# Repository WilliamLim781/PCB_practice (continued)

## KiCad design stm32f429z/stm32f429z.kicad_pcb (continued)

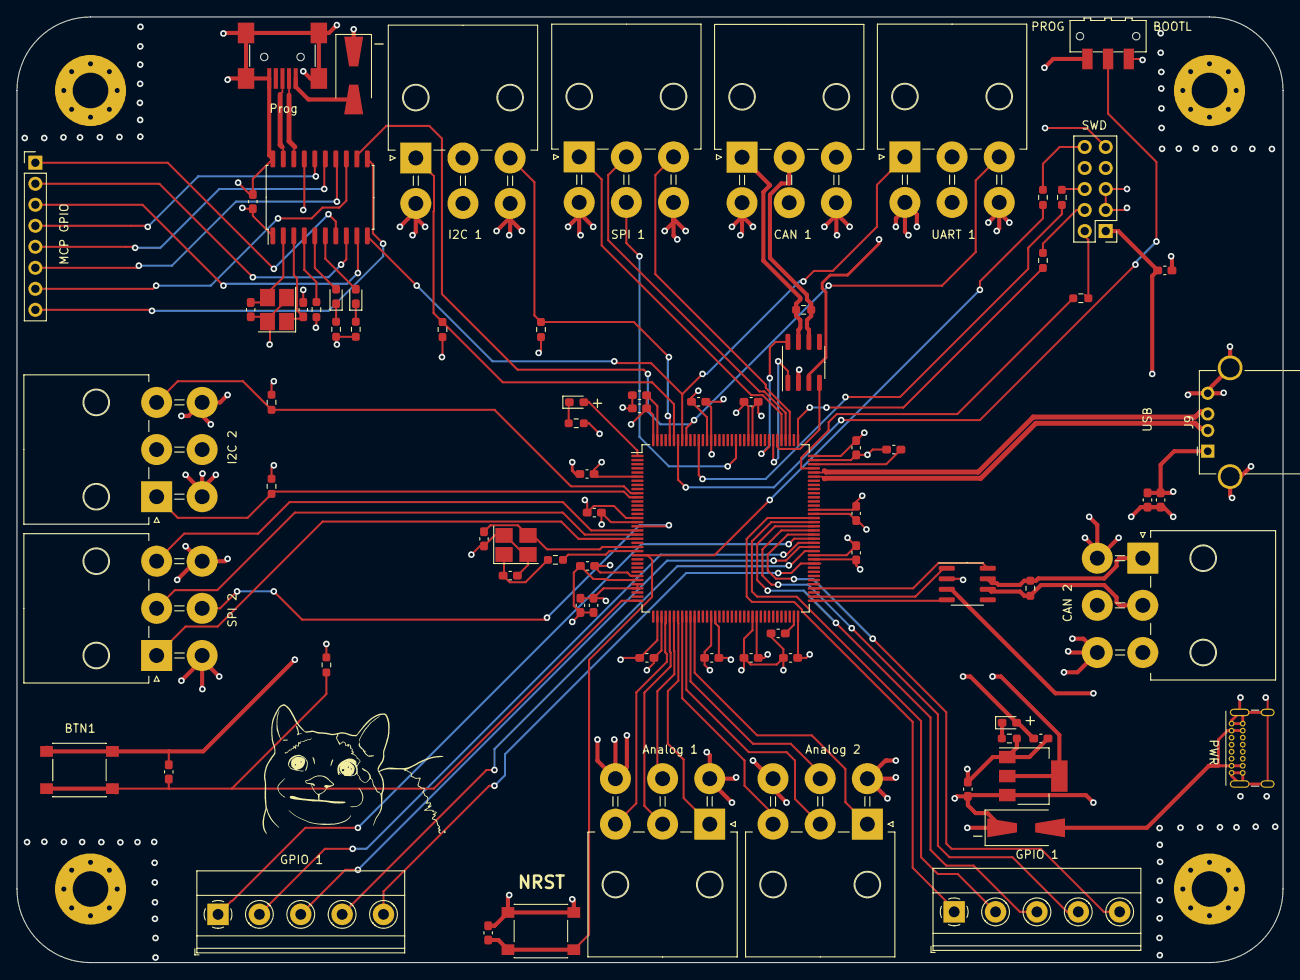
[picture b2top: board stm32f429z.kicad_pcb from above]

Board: 4 copper layers, 153.0 x 114.3 mm, 83 parts (0 on the bottom side), 84 nets.

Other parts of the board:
C26: 10u; C_0603_1608Metric_Pad1.08x0.95mm_HandSolder
C27: 22u; C_0603_1608Metric_Pad1.08x0.95mm_HandSolder
D4: LED; LED_0603_1608Metric_Pad1.05x0.95mm_HandSolder
J9: USB_A; USB_A_Stewart_SS-52100-001_Horizontal
P2: USB_C_Plug_USB2.0; USB_C_Receptacle_GCT_USB4085
R16, R17: 2k2; R_0603_1608Metric_Pad0.98x0.95mm_HandSolder
SW4: Logging BTN; SW_SPST_PTS645
U6: AMS1117-3.3; SOT-223-3_TabPin2

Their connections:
unnamed: D4.1 (K), R16.1
unnamed 47: P2.A4 (VBUS), P2.A9 (VBUS), P2.B4 (VBUS), P2.B9 (VBUS); also elsewhere on the board
USB_OTG_FS_DP+: J9.3 (D+); also elsewhere on the board
USB_OTG_FS_DP-: J9.2 (D-); also elsewhere on the board

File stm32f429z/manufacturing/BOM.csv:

Comment,Designator,Footprint ,JLCPCB Part #
14pF,"C1, C2",603,C5360816
100nF,"C3-14, C16, C20, C22, C23, C28",603,C76599
4.7uF,"C15, C21",603,C19666
10nF,C17,603,C57112
1uF,C18,603,C15849
500nF,C19,603,C124567
6pF," C24, C25",603,C282508
10uF,C26,603,C96446
22uF,"C27, C29, C30",603,C96446
LED,D1-4,603,C72038
Schottky ," D5, D6",603,C2480
0, R1,603,C441885
100, R2-5,603,C427273
2.2k,"R6-9, R14-R17",603,C2906988
120," R10, R11",603,C4226066
10k,R12,603,C473239
4.7K,R13,603,C473239
STM32F429ZITx,U1,LQFP-144,C92002
TJA1051T,"U2, U3",SOIC-8,C38695
16Mhz,X1,SMD_3225,C12668
,H1-4,,
,J1-5,,
,J6,,
,J7,,
,J8,,
,J10,,
,J12,,
,J13,,
,J14,,
,J15 -16,,
,P2,,
,SW1 ,,
,SW2,,
,SW4,,
,U2-3,,
,U5,,
,U6,,
,X1,,
,Y1,,

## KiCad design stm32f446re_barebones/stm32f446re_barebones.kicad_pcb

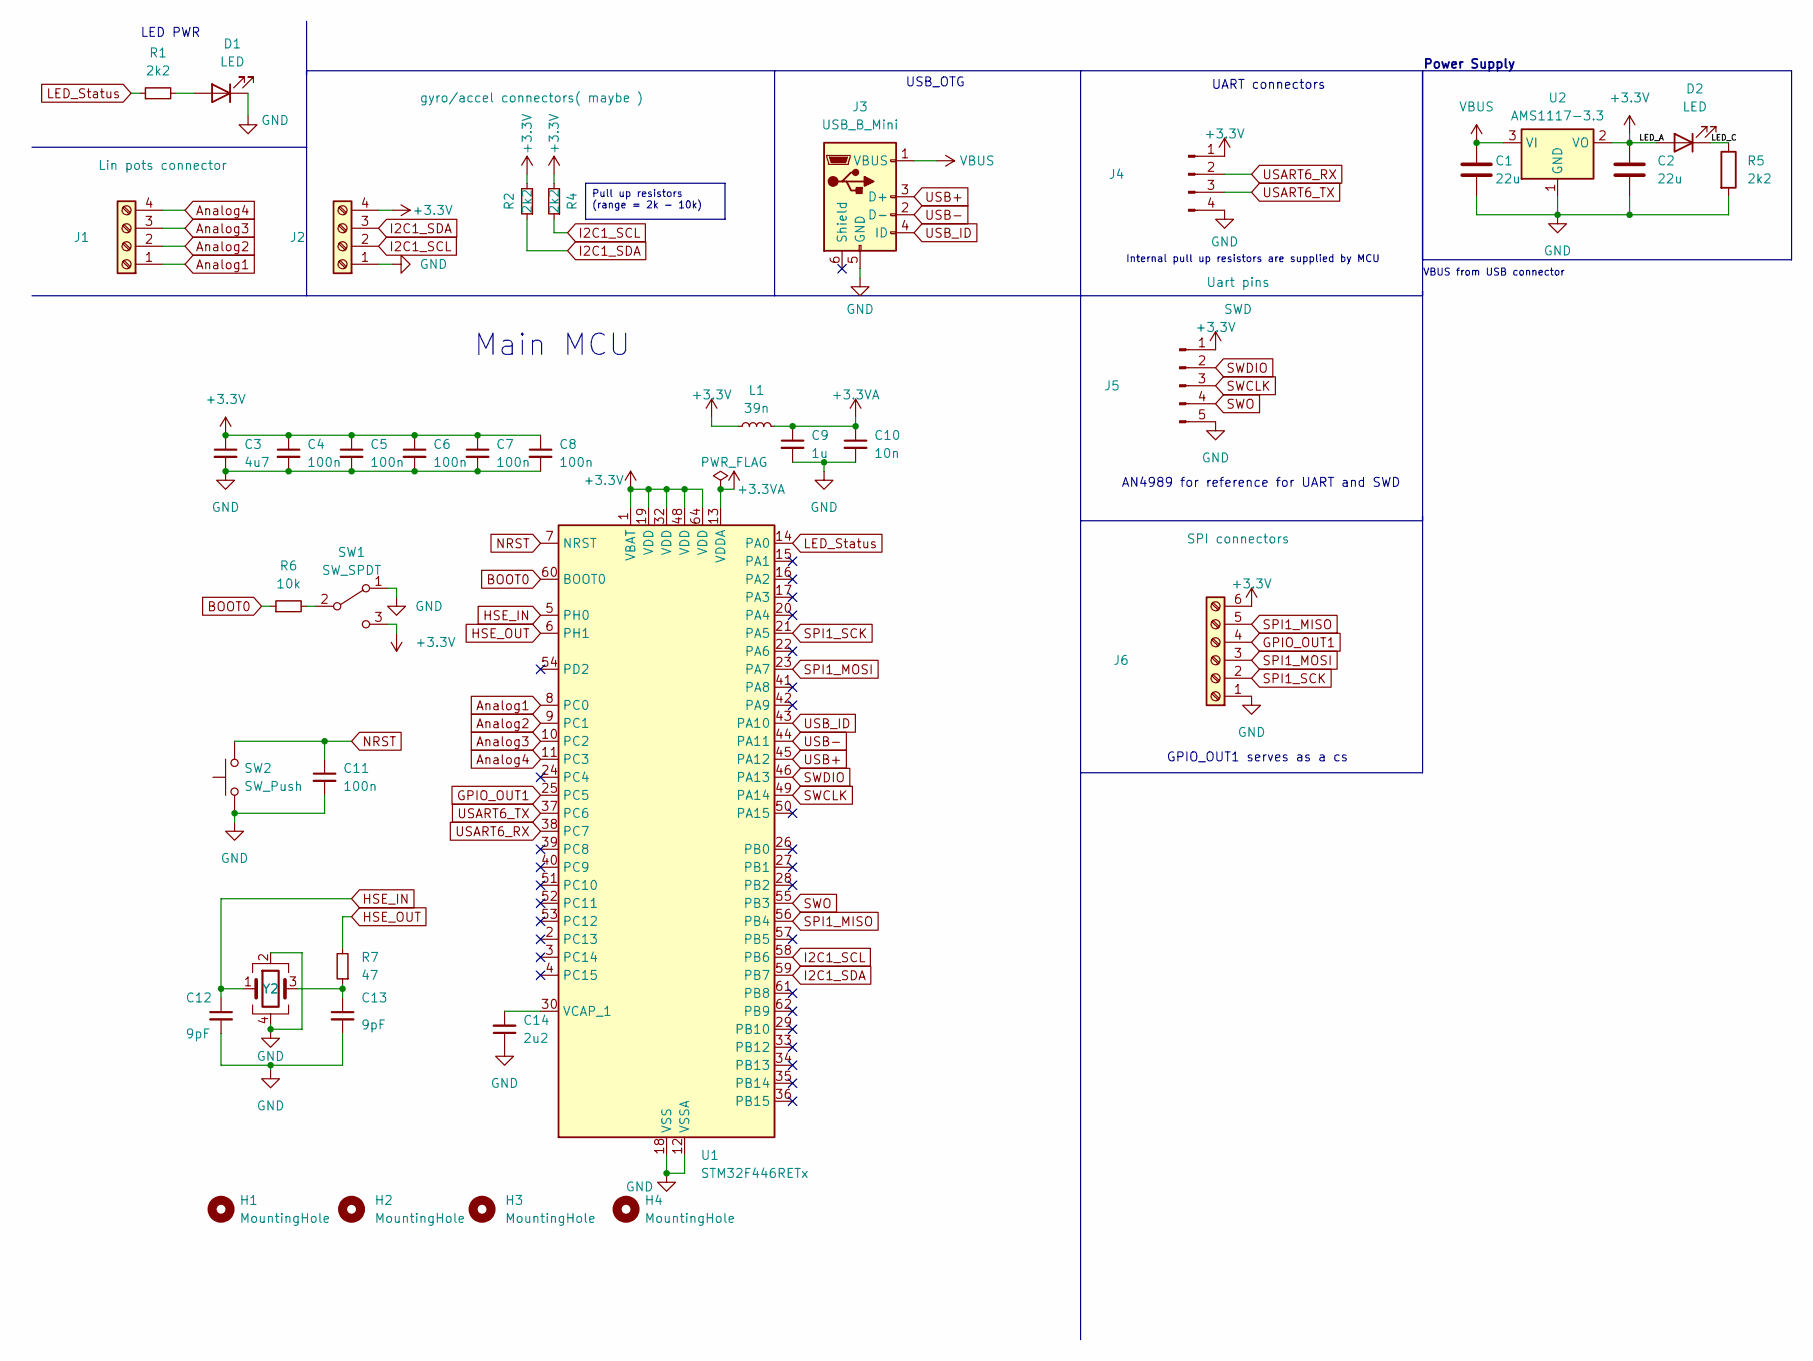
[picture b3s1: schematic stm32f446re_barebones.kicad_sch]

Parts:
C1, C2: 22u; C_0603_1608Metric
C3: 4u7; C_0603_1608Metric
C4, C5, C6, C7, C8, C11: 100n; C_0603_1608Metric
C9: 1u; C_0603_1608Metric
C10: 10n; C_0603_1608Metric
C12, C13: 9pF; C_0603_1608Metric
C14: 2u2; C_0603_1608Metric
D1, D2: LED; LED_1210_3225Metric
H1, H2, H3, H4: MountingHole; MountingHole_2.2mm_M2_DIN965_Pad
J1: Lin pots connector; TerminalBlock_Phoenix_MKDS-1,5-4_1x04_P5.00mm_Horizontal
J2: gyro/accel connectors( maybe ); TerminalBlock_Phoenix_MKDS-1,5-4_1x04_P5.00mm_Horizontal
J3: USB_B_Mini; USB_Mini-B_Lumberg_2486_01_Horizontal
J4: Uart pins; PinHeader_1x04_P2.54mm_Horizontal
J5: SWD; PinHeader_1x05_P2.54mm_Horizontal
J6: SPI connectors; TerminalBlock_Phoenix_MKDS-1,5-6-5.08_1x06_P5.08mm_Horizont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
L1: 39n; L_0805_2012Metric
R1, R2, R4: 2k2; R_0805_2012Metric
R5: 2k2; R_0402_1005Metric_Pad0.72x0.64mm_HandSolder
R6: 10k; R_0805_2012Metric
R7: 47; R_0805_2012Metric
SW1: SW_SPDT; SW_SPDT_PCM12
SW2: SW_Push; SW_SPST_B3U-1000P-B
U1: STM32F446RETx; LQFP-64_10x10mm_P0.5mm
U2: AMS1117-3.3; SOT-223-3_TabPin2
Y2: Y2; Crystal_SMD_3225-4Pin_3.2x2.5mm

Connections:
+3.3V: C2.1, C3.1, C4.1, C5.1, C6.1, C7.1, C8.1, D2.2 (A), J2.4, J4.1, J5.1, J6.6, L1.1, R2.2, R4.2, SW1.3 (C), U1.1 (VBAT), U1.19 (VDD), U1.32 (VDD), U1.48 (VDD), U1.64 (VDD), U2.2 (VO)
+3.3VA: C9.1, C10.1, L1.2, U1.13 (VDDA)
/LED_C: D2.1 (K), R5.1
Analog1: J1.1, U1.8 (PC0)
Analog2: J1.2, U1.9 (PC1)
Analog3: J1.3, U1.10 (PC2)
Analog4: J1.4, U1.11 (PC3)
BOOT0: R6.1, U1.60 (BOOT0)
GND: C1.2, C2.2, C3.2, C4.2, C5.2, C6.2, C7.2, C8.2, C9.2, C10.2, C11.2, C12.2, C13.2, C14.1, D1.1 (K), J2.1, J3.5 (GND), J4.4, J5.5, J6.1, R5.2, SW1.1 (A), SW2.1, U1.12 (VSSA), U1.18 (VSS), U1.31 (VSS), U1.47 (VSS), U1.63 (VSS), U2.1 (GND), Y2.2, Y2.4
GPIO_OUT1: J6.4, U1.25 (PC5)
HSE_IN: C12.1, U1.5 (PH0), Y2.1
HSE_OUT: R7.2, U1.6 (PH1)
I2C1_SCL: J2.2, R4.1, U1.58 (PB6)
I2C1_SDA: J2.3, R2.1, U1.59 (PB7)
LED_Status: R1.1, U1.14 (PA0)
NRST: C11.1, SW2.2, U1.7 (NRST)
unnamed: C13.1, R7.1, Y2.3
unnamed: D1.2 (A), R1.2
unnamed: R6.2, SW1.2 (B)
unnamed: C14.2, U1.30 (VCAP_1)
SPI1_MISO: J6.5, U1.56 (PB4)
SPI1_MOSI: J6.3, U1.23 (PA7)
SPI1_SCK: J6.2, U1.21 (PA5)
SWCLK: J5.3, U1.49 (PA14)
SWDIO: J5.2, U1.46 (PA13)
SWO: J5.4, U1.55 (PB3)
USART6_RX: J4.2, U1.38 (PC7)
USART6_TX: J4.3, U1.37 (PC6)
USB+: J3.3 (D+), U1.45 (PA12)
USB-: J3.2 (D-), U1.44 (PA11)
USB_ID: J3.4 (ID), U1.43 (PA10)
VBUS: C1.1, J3.1 (VBUS), U2.3 (VI)

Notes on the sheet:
Pull up resistors (range = 2k - 10k)
Power Supply
Internal pull up resistors are supplied by MCU
VBUS from USB connector
LED PWR
AN4989 for reference for UART and SWD
Main MCU
UART connectors
USB_OTG
GPIO_OUT1 serves as a cs

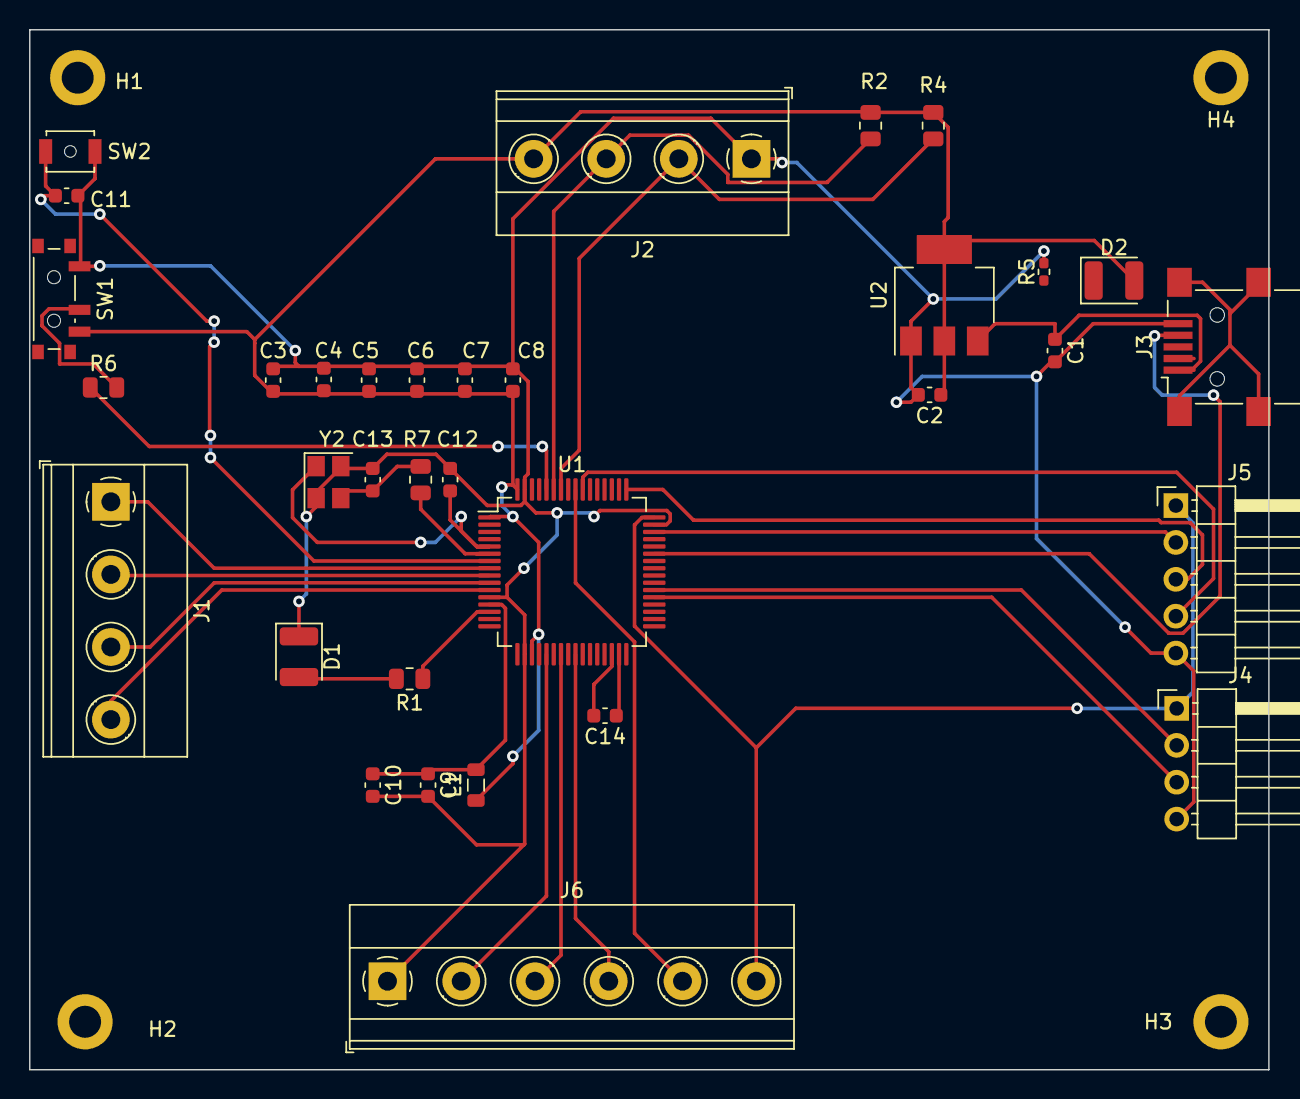
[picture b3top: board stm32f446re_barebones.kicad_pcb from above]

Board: 2 copper layers, 85.3 x 71.6 mm, 38 parts (0 on the bottom side), 32 nets.
